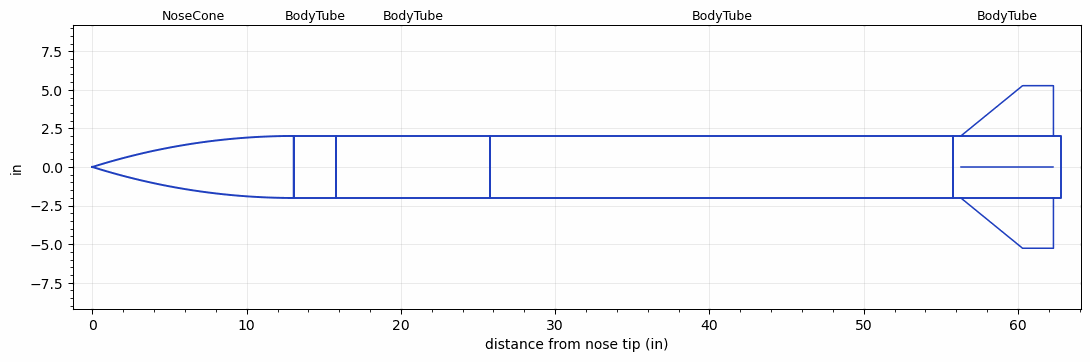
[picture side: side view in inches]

<RASAeroDocument>
 <FileVersion>2</FileVersion>
 <RocketDesign>
  <NoseCone>
   <Length>13.05</Length>
   <Diameter>4.02</Diameter>
   <Shape>Tangent Ogive</Shape>
   <Location>0</Location>
  </NoseCone>
  <BodyTube>
   <Length>2.75</Length>
   <Diameter>4.02</Diameter>
   <Location>13.05</Location>
  </BodyTube>
  <BodyTube>
   <Length>10</Length>
   <Diameter>4.02</Diameter>
   <Location>15.8</Location>
  </BodyTube>
  <BodyTube>
   <Length>29.9999</Length>
   <Diameter>4.02</Diameter>
   <Location>25.8</Location>
   <Protuberance>
    <StreamlinedNoBaseDrag>0.369</StreamlinedNoBaseDrag>
    <StreamlinedWithBaseDrag>0</StreamlinedWithBaseDrag>
    <InclinedPlate1Angle>0</InclinedPlate1Angle>
    <InclinedPlate1FrontalArea>0</InclinedPlate1FrontalArea>
    <InclinedPlate2Angle>0</InclinedPlate2Angle>
    <InclinedPlate2FrontalArea>0</InclinedPlate2FrontalArea>
   </Protuberance>
  </BodyTube>
  <BodyTube>
   <Length>7</Length>
   <Diameter>4.02</Diameter>
   <Location>55.7999</Location>
   <Fin>
    <Count>4</Count>
    <Chord>6</Chord>
    <Span>3.26</Span>
    <SweepDistance>4</SweepDistance>
    <TipChord>2</TipChord>
    <Thickness>0.37</Thickness>
    <Location>6.5</Location>
    <AirfoilSection>Hexagonal Blunt Base</AirfoilSection>
    <FX1>0.7</FX1>
   </Fin>
  </BodyTube>
  <Surface>Rough Camouflage Paint</Surface>
  <ModifiedBarrowman>False</ModifiedBarrowman>
  <Turbulence>False</Turbulence>
  <UseBooster1>False</UseBooster1>
  <UseBooster2>False</UseBooster2>
 </RocketDesign>
 <LaunchSite>
  <Altitude>0</Altitude>
  <Pressure>29.9214</Pressure>
  <RodAngle>0</RodAngle>
  <RodLength>3.2808</RodLength>
  <Temperature>59</Temperature>
  <WindSpeed>4.4739</WindSpeed>
 </LaunchSite>
 <Recovery>
  <Altitude1>656.168</Altitude1>
  <Altitude2>0</Altitude2>
  <DeviceType1>Parachute</DeviceType1>
  <DeviceType2>None</DeviceType2>
  <Event1>True</Event1>
  <Event2>False</Event2>
  <Size1>24</Size1>
  <Size2>0</Size2>
  <EventType1>Apogee</EventType1>
  <EventType2>None</EventType2>
  <CD1>0.8</CD1>
  <CD2>0</CD2>
 </Recovery>
 <SimulationList>
  <Simulation>
   <SustainerEngine>I500T-14A  (AT)</SustainerEngine>
   <SustainerLaunchWt>14.38</SustainerLaunchWt>
   <SustainerCG>40.07</SustainerCG>
   <SustainerIgnitionDelay>0</SustainerIgnitionDelay>
   <Booster1SeparationDelay>0</Booster1SeparationDelay>
   <Booster1IgnitionDelay>0</Booster1IgnitionDelay>
   <IncludeBooster1>False</IncludeBooster1>
   <Booster2Delay>0</Booster2Delay>
   <IncludeBooster2>False</IncludeBooster2>
   <TimetoApogee>9.180115</TimetoApogee>
   <MaxAltitude>1238.354</MaxAltitude>
   <MaxVelocity>272.9196</MaxVelocity>
  </Simulation>
  <Simulation>
   <SustainerEngine>J570W  (AT)</SustainerEngine>
   <SustainerLaunchWt>15.0538</SustainerLaunchWt>
   <SustainerCG>40.466</SustainerCG>
   <SustainerIgnitionDelay>0</SustainerIgnitionDelay>
   <Booster1SeparationDelay>0</Booster1SeparationDelay>
   <Booster1IgnitionDelay>0</Booster1IgnitionDelay>
   <IncludeBooster1>False</IncludeBooster1>
   <Booster2Delay>0</Booster2Delay>
   <IncludeBooster2>False</IncludeBooster2>
   <TimetoApogee>13.41021</TimetoApogee>
   <MaxAltitude>2867.387</MaxAltitude>
   <MaxVelocity>433.9009</MaxVelocity>
  </Simulation>
 </SimulationList>
</RASAeroDocument>
